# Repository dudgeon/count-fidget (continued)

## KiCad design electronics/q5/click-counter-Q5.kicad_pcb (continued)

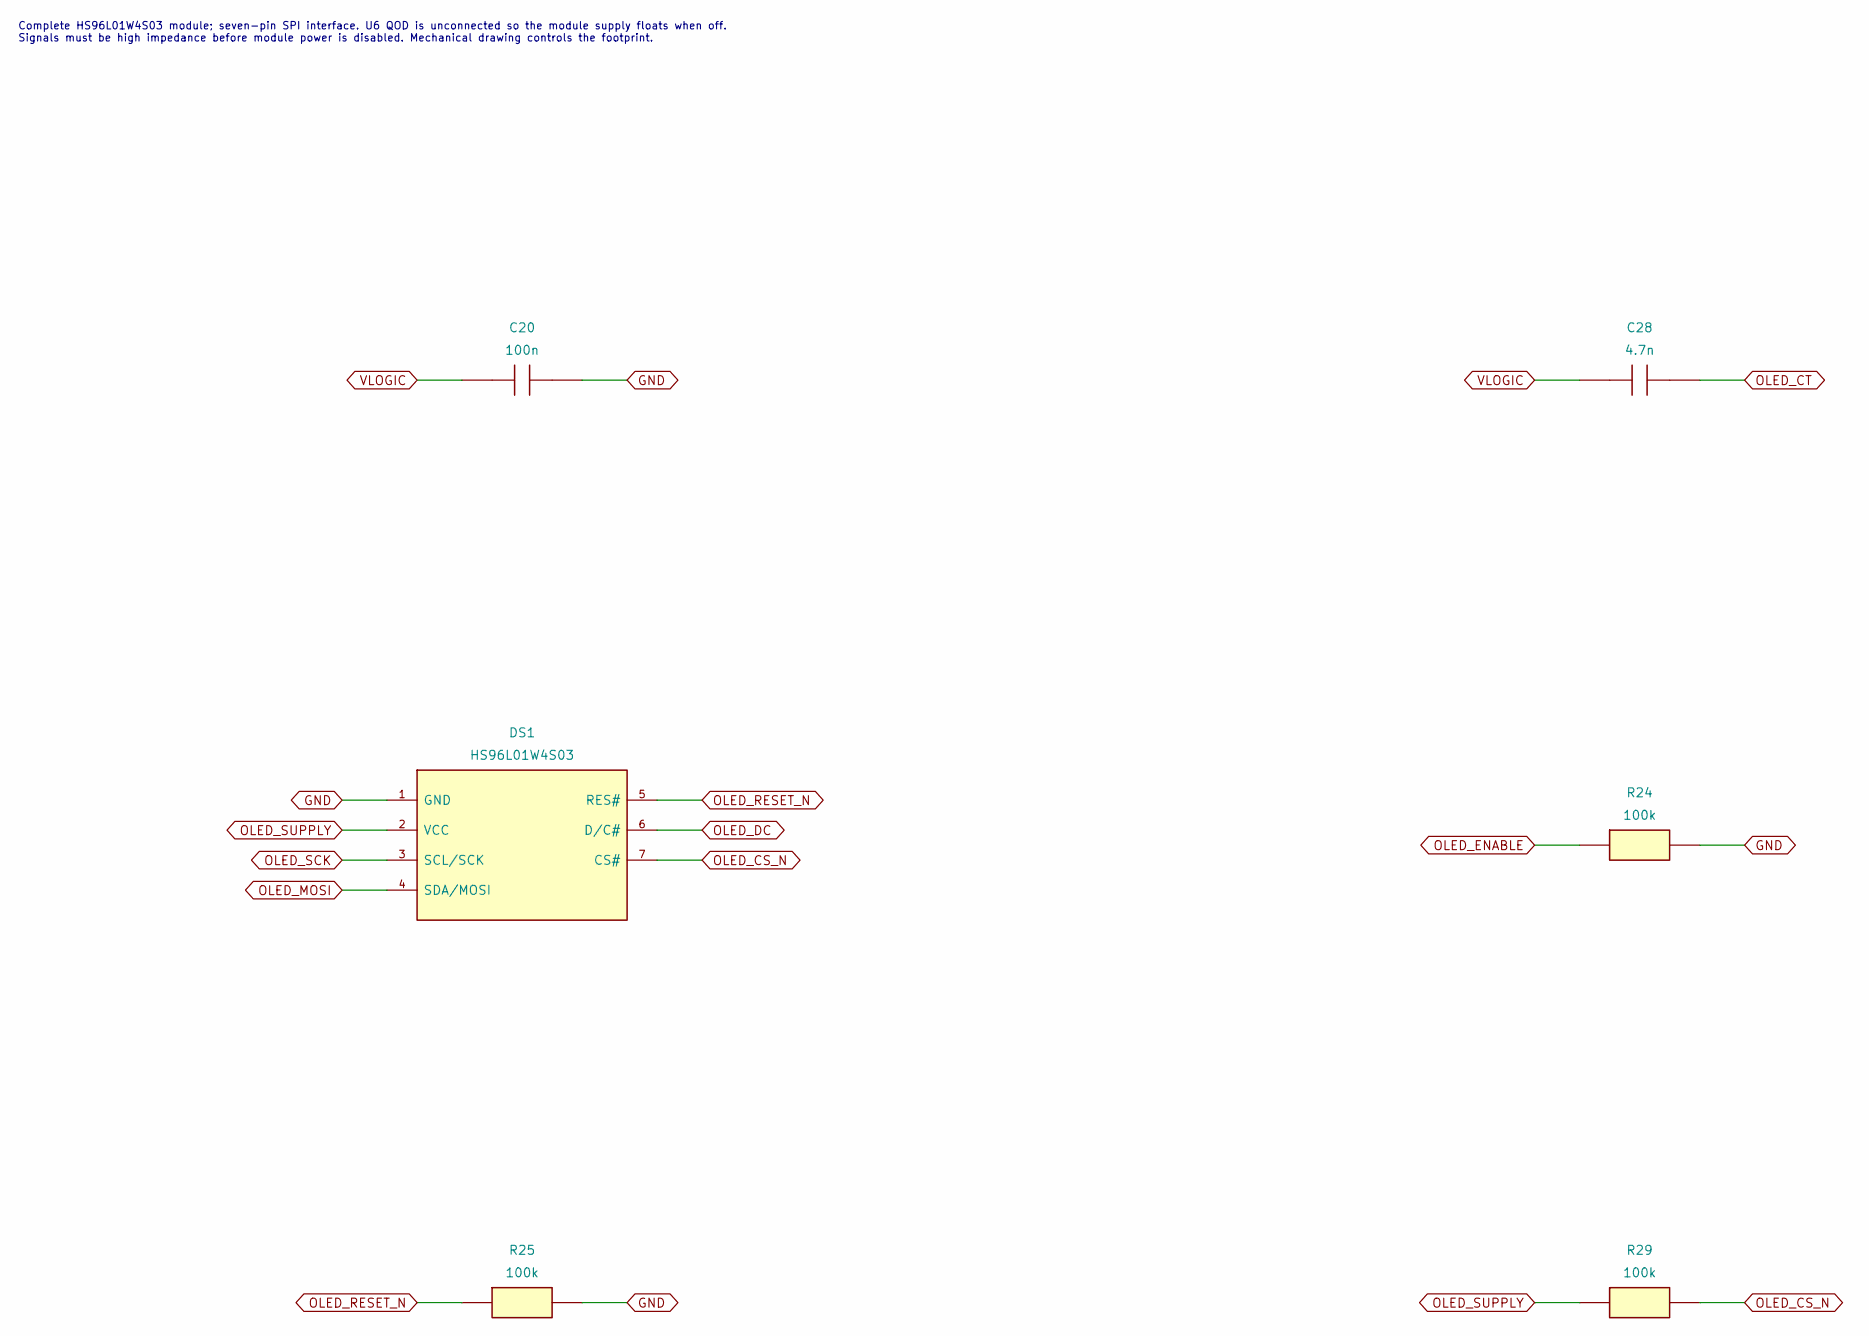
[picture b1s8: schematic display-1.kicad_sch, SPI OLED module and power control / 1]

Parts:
C20: 100n; Capacitor_SMD_C_0603_1608Metric; MPN CC0603KRX7R9BB104
C28: 4.7n; Capacitor_SMD_C_0603_1608Metric; MPN 0603B472K500NT
DS1: SPI OLED module 128x64; HS96L01W4S03_Module_7Pin; MPN HS96L01W4S03
R24, R25, R29: 100k; Resistor_SMD_R_0603_1608Metric; MPN 0603WAF1003T5E

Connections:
GND: C20.2, DS1.1 (GND), R24.2, R25.2; also elsewhere on the board
OLED_CS_N: DS1.7 (CS#), R29.2; also elsewhere on the board
OLED_CT: C28.2; also elsewhere on the board
OLED_DC: DS1.6 (D/C#); also elsewhere on the board
OLED_ENABLE: R24.1; also elsewhere on the board
OLED_MOSI: DS1.4 (SDA/MOSI); also elsewhere on the board
OLED_RESET_N: DS1.5 (RES#), R25.1; also elsewhere on the board
OLED_SCK: DS1.3 (SCL/SCK); also elsewhere on the board
OLED_SUPPLY: DS1.2 (VCC), R29.1; also elsewhere on the board
VLOGIC: C20.1, C28.1; also elsewhere on the board

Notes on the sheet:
Complete HS96L01W4S03 module; seven-pin SPI interface. U6 QOD is unconnected so the module supply floats when off. Signals must be high impedance before module power is disabled. Mechanical drawing controls the footprint.

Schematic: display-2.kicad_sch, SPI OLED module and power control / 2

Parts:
U6: OLED power slew switch; Package_TO_SOT_SMD_SOT-23-6; MPN TPS22917DBVR

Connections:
GND: U6.2 (GND); also elsewhere on the board
OLED_CT: U6.4 (CT); also elsewhere on the board
OLED_ENABLE: U6.3 (ON); also elsewhere on the board
OLED_SUPPLY: U6.6 (VOUT); also elsewhere on the board
VLOGIC: U6.1 (VIN); also elsewhere on the board

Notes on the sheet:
Complete HS96L01W4S03 module; seven-pin SPI interface. U6 QOD is unconnected so the module supply floats when off. Signals must be high impedance before module power is disabled. Mechanical drawing controls the footprint.

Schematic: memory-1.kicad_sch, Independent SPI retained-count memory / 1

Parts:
C30: 10u; Capacitor_SMD_C_0805_2012Metric; MPN GRM21BR61H106KE43L
C36: 100n; Capacitor_SMD_C_0603_1608Metric; MPN CC0603KRX7R9BB104
R32: 75; Resistor_SMD_R_0603_1608Metric; MPN 0603WAF750JT5E
R33: 100k; Resistor_SMD_R_0603_1608Metric; MPN 0603WAF1003T5E
U8: SPI F-RAM 32KiB; Package_SO_SOIC-8_3.9x4.9mm_P1.27mm; MPN FM25V02A-GTR

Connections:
FRAM_CS_N: R33.2, U8.1 (CS#); also elsewhere on the board
FRAM_MISO: U8.2 (SO); also elsewhere on the board
FRAM_MOSI: U8.5 (SI); also elsewhere on the board
FRAM_SCK: U8.6 (SCK); also elsewhere on the board
GND: C30.2, C36.2, U8.4 (VSS); also elsewhere on the board
VFRAM: C30.1, C36.1, R32.2, R33.1, U8.3 (WP#), U8.7 (HOLD#), U8.8 (VDD)
VLOGIC: R32.1; also elsewhere on the board

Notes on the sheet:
FM25V02A F-RAM on an isolated RC supply; dedicated SPI1. Power-ramp, chip-select and interrupted-write behavior require separate analysis and physical qualification.

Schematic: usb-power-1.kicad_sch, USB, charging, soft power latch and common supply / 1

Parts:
C1, C3: 2.2u; Capacitor_SMD_C_0805_2012Metric; MPN CL21A225KBQNNNE
C2: 10u; Capacitor_SMD_C_0805_2012Metric; MPN GRM21BR61H106KE43L
C13, C29: 4.7n; Capacitor_SMD_C_0603_1608Metric; MPN 0603B472K500NT
C38: 100n; Capacitor_SMD_C_0603_1608Metric; MPN CC0603KRX7R9BB104

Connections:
CELL_P: C3.1; also elsewhere on the board
GND: C1.2, C2.2, C3.2, C13.2, C38.2; also elsewhere on the board
RC_COMP: C13.1; also elsewhere on the board
SYS: C2.1, C29.1; also elsewhere on the board
SYS_CT: C29.2; also elsewhere on the board
VBUS: C1.1, C38.1; also elsewhere on the board

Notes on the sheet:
U7 ON = VBUS (D4) OR COUNT key (D3 A1) OR PWR_HOLD (D3 A2), pulled down by R35. Off: only BQ29700 and BQ25185 battery quiescent current remain. Cold cell insertion is not proven by the slew switch.

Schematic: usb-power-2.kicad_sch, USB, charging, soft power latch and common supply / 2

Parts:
C5: 2.2u; Capacitor_SMD_C_0805_2012Metric; MPN CL21A225KBQNNNE
C39: 100n; Capacitor_SMD_C_0603_1608Metric; MPN CC0603KRX7R9BB104
C40: 10n; Capacitor_SMD_C_0603_1608Metric; MPN 0603B103K500NT
D1, D2: USB ESD; Package_TO_SOT_SMD_SOT-23-6; MPN USBLC6-2SC6
D3: BAT54C; Package_TO_SOT_SMD_SOT-23; MPN BAT54C,215

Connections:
CC1: D1.1 (I/O1), D1.6 (I/O1); also elsewhere on the board
CC2: D1.3 (I/O2), D1.4 (I/O2); also elsewhere on the board
GND: C5.2, C39.2, C40.2, D1.2 (GND), D2.2 (GND); also elsewhere on the board
PWR_HOLD: D3.2 (A2); also elsewhere on the board
PWR_KEY: D3.1 (A1); also elsewhere on the board
SYS_LOAD: C5.1; also elsewhere on the board
SYS_ON: C40.1, D3.3 (K); also elsewhere on the board
USB_DM: D2.1 (I/O1), D2.6 (I/O1); also elsewhere on the board
USB_DP: D2.3 (I/O2), D2.4 (I/O2); also elsewhere on the board
VBUS: C39.1, D1.5 (VBUS), D2.5 (VBUS); also elsewhere on the board

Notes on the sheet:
U7 ON = VBUS (D4) OR COUNT key (D3 A1) OR PWR_HOLD (D3 A2), pulled down by R35. Off: only BQ29700 and BQ25185 battery quiescent current remain. Cold cell insertion is not proven by the slew switch.

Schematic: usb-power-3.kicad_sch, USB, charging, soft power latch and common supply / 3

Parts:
D4: 1N4148WS; Diode_SMD_D_SOD-323; MPN 1N4148WS
J1: USB-C power and DFU; Connector_USB_USB_C_Receptacle_GCT_USB4105-xx-A_16P_TopMnt_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; MPN USB4105-GF-A-120
R1, R2: 5.1k; Resistor_SMD_R_0603_1608Metric; MPN 0603WAF5101T5E
R3: 24k; Resistor_SMD_R_0603_1608Metric; MPN 0603WAF2402T5E
R19: 2k; Resistor_SMD_R_0603_1608Metric; MPN 0603WAF2001T5E

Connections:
CC1: J1.A5 (CCA), R1.1; also elsewhere on the board
CC2: J1.B5 (CCB), R2.1; also elsewhere on the board
GND: J1.A1 (GND), J1.A12 (GND), J1.B1 (GND), J1.B12 (GND), J1.SH (SHIELD), R1.2, R2.2, R3.2; also elsewhere on the board
ISET: R19.1; also elsewhere on the board
RC_COMP: R19.2; also elsewhere on the board
USB_DM: J1.A7 (D-), J1.B7 (D-); also elsewhere on the board
USB_DP: J1.A6 (D+), J1.B6 (D+); also elsewhere on the board
VBUS: D4.2 (A), J1.A4 (VBUS), J1.A9 (VBUS), J1.B4 (VBUS), J1.B9 (VBUS); also elsewhere on the board
VBUS_WAKE: D4.1 (K); also elsewhere on the board
VSET: R3.1; also elsewhere on the board

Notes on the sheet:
U7 ON = VBUS (D4) OR COUNT key (D3 A1) OR PWR_HOLD (D3 A2), pulled down by R35. Off: only BQ29700 and BQ25185 battery quiescent current remain. Cold cell insertion is not proven by the slew switch.

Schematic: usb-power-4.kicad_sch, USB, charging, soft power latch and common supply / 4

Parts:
R4: 18k; Resistor_SMD_R_0603_1608Metric; MPN 0603WAF1802T5E
R30: 150k; Resistor_SMD_R_0603_1608Metric; MPN RT0603BRD07150KL
R31: 49.9k; Resistor_SMD_R_0603_1608Metric; MPN RT0603BRD0749K9L
R34, R38: 100k; Resistor_SMD_R_0603_1608Metric; MPN 0603WAF1003T5E
R35: 1M; Resistor_SMD_R_0603_1608Metric; MPN 0603WAF1004T5E

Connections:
GND: R4.2, R31.2, R34.2, R35.2; also elsewhere on the board
ISET: R4.1; also elsewhere on the board
PWR_KEY: R34.1; also elsewhere on the board
SYS_ON: R35.1, R38.2; also elsewhere on the board
VBUS_WAKE: R38.1; also elsewhere on the board
VLOGIC: R30.1; also elsewhere on the board
VLOGIC_FB: R30.2, R31.1; also elsewhere on the board

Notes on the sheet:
U7 ON = VBUS (D4) OR COUNT key (D3 A1) OR PWR_HOLD (D3 A2), pulled down by R35. Off: only BQ29700 and BQ25185 battery quiescent current remain. Cold cell insertion is not proven by the slew switch.

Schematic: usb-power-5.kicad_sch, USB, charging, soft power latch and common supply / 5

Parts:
R5: 10k; Resistor_SMD_R_0603_1608Metric; MPN 0603WAF1002T5E
R6: 100k; Resistor_SMD_R_0603_1608Metric; MPN 0603WAF1003T5E
TP13: SYS_ON; TestPoint_TestPoint_Pad_D1.5mm; MPN PCB LAND
U2: Li-ion charger; Package_DFN_QFN_Texas_DLH0010A_WSON-10-1EP_2.2x2mm_P0.4mm_E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; MPN BQ25185DLHR
U3: 3.20481V adjustable LDO; Package_SON_WSON-6-1EP_2x2mm_P0.65mm_EP1x1.6mm; MPN TLV76701DRVR
U7: System soft-power latch switch; Package_TO_SOT_SMD_SOT-23-6; MPN TPS22917DBVR

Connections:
CELL_P: U2.2 (BAT); also elsewhere on the board
CE_N: R6.2, U2.4 (~CE); also elsewhere on the board
CHG_STAT1: U2.9 (STAT1); also elsewhere on the board
CHG_STAT2: U2.3 (STAT2); also elsewhere on the board
GND: R5.2, U2.5 (GND), U2.11 (EP/GND), U3.3 (GND), U3.5 (GND), U3.7 (EP), U7.2 (GND); also elsewhere on the board
ISET: U2.8 (ISET); also elsewhere on the board
SYS: U2.1 (SYS), U7.1 (VIN); also elsewhere on the board
SYS_CT: U7.4 (CT); also elsewhere on the board
SYS_LOAD: U3.4 (EN), U3.6 (IN), U7.6 (VOUT); also elsewhere on the board
SYS_ON: TP13.1 (1_1), U7.3 (ON); also elsewhere on the board
TS_FIXED: R5.1, U2.6 (TS/MR)
VBUS: R6.1, U2.10 (IN); also elsewhere on the board
VLOGIC: U3.1 (OUT); also elsewhere on the board
VLOGIC_FB: U3.2 (FB); also elsewhere on the board
VSET: U2.7 (ILIM/VSET); also elsewhere on the board

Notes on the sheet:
U7 ON = VBUS (D4) OR COUNT key (D3 A1) OR PWR_HOLD (D3 A2), pulled down by R35. Off: only BQ29700 and BQ25185 battery quiescent current remain. Cold cell insertion is not proven by the slew switch.

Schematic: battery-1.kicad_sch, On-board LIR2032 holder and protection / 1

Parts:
BT1: LIR2032 holder; BatteryHolder_QJ_CR2032-BS-6-1; MPN CR2032-BS-6-1
C4: 100n; Capacitor_SMD_C_0603_1608Metric; MPN CC0603KRX7R9BB104
Q1: Discharge FET; Package_TO_SOT_SMD_SOT-23; MPN AO3400A
Q2: Charge FET; Package_TO_SOT_SMD_SOT-23; MPN AO3400A
R7: 330; Resistor_SMD_R_0603_1608Metric; MPN 0603WAF3300T5E
R8: 2.2k; Resistor_SMD_R_0603_1608Metric; MPN 0603WAF2201T5E

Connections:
BAT_SENSE: C4.1, R7.2; also elsewhere on the board
CELL_N_RAW: BT1.2 (-), C4.2, Q1.2 (S); also elsewhere on the board
CELL_P: BT1.1 (+), R7.1; also elsewhere on the board
COUT: Q2.1 (G); also elsewhere on the board
DOUT: Q1.1 (G); also elsewhere on the board
FET_DRAIN: Q1.3 (D), Q2.3 (D)
GND: R8.1; also elsewhere on the board
SENSE_FET: Q2.2 (S); also elsewhere on the board
VMINUS: R8.2; also elsewhere on the board

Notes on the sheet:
CELL_N_RAW is isolated from system ground by the protection path. BT1 accepts the rechargeable LIR2032 only. Cell compatibility, protection, USB rearm and cold insertion remain qualification gates.

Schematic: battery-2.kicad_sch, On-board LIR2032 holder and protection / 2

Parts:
R9: 3.3; Resistor_SMD_R_0603_1608Metric; MPN 0603WAF330KT5E
U4: Cell protector; Package_SON_WSON-6_1.5x1.5mm_P0.5mm; MPN BQ29700DSER

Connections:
BAT_SENSE: U4.5 (BAT); also elsewhere on the board
CELL_N_RAW: U4.4 (VSS); also elsewhere on the board
COUT: U4.2 (COUT); also elsewhere on the board
DOUT: U4.3 (DOUT); also elsewhere on the board
GND: R9.2; also elsewhere on the board
SENSE_FET: R9.1; also elsewhere on the board
VMINUS: U4.6 (V-); also elsewhere on the board

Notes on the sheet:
CELL_N_RAW is isolated from system ground by the protection path. BT1 accepts the rechargeable LIR2032 only. Cell compatibility, protection, USB rearm and cold insertion remain qualification gates.

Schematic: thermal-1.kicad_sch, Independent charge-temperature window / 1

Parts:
C9: 100n; Capacitor_SMD_C_0603_1608Metric; MPN CC0603KRX7R9BB104
Q3: Charge enable; Package_TO_SOT_SMD_SOT-23; MPN 2N7002
Q4: Charge enable hot gate; Package_TO_SOT_SMD_SOT-23; MPN 2N7002
R10: 56k; Resistor_SMD_R_0603_1608Metric; MPN 0603WAF5602T5E
R11: 82k; Resistor_SMD_R_0603_1608Metric; MPN 0603WAF8202T5E
R12: 18k; Resistor_SMD_R_0603_1608Metric; MPN 0603WAF1802T5E

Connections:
CE_MID: Q3.2 (S), Q4.3 (D)
CE_N: Q3.3 (D); also elsewhere on the board
GND: C9.2, Q4.2 (S); also elsewhere on the board
TEMP_COLD: R11.2, R12.1; also elsewhere on the board
TEMP_COLD_OK: Q3.1 (G); also elsewhere on the board
TEMP_HOT: R12.2; also elsewhere on the board
TEMP_HOT_OK: Q4.1 (G); also elsewhere on the board
TEMP_SENSE: R10.2; also elsewhere on the board
U5_VCC: C9.1; also elsewhere on the board
VBUS: R10.1, R11.1; also elsewhere on the board

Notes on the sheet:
TH1 on the board beside BT1; both window outputs must enable their series FETs for charging. Gate pulldowns disable charging when comparator power is absent; threshold and fault tests remain required.

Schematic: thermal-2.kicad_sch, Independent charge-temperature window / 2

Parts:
R13: 12k; Resistor_SMD_R_0603_1608Metric; MPN 0603WAF1202T5E
R14, R15: 100k; Resistor_SMD_R_0603_1608Metric; MPN 0603WAF1003T5E
R39: 1k; Resistor_SMD_R_0603_1608Metric; MPN 0603WAF1001T5E
TH1: 10k NTC B3380; Resistor_SMD_R_0603_1608Metric; MPN NCP18XH103F03RB
U5: Push-pull temperature window; Package_TO_SOT_SMD_SOT-23-8; MPN TLV7012DDFR

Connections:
GND: R13.2, R14.2, R15.2, TH1.2, U5.4 (VEE); also elsewhere on the board
TEMP_COLD: U5.3 (INA+); also elsewhere on the board
TEMP_COLD_OK: R14.1, U5.1 (OUTA); also elsewhere on the board
TEMP_HOT: R13.1, U5.6 (INB-); also elsewhere on the board
TEMP_HOT_OK: R15.1, U5.7 (OUTB); also elsewhere on the board
TEMP_SENSE: TH1.1, U5.2 (INA-), U5.5 (INB+); also elsewhere on the board
U5_VCC: R39.2, U5.8 (VCC); also elsewhere on the board
VBUS: R39.1; also elsewhere on the board

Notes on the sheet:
TH1 on the board beside BT1; both window outputs must enable their series FETs for charging. Gate pulldowns disable charging when comparator power is absent; threshold and fault tests remain required.

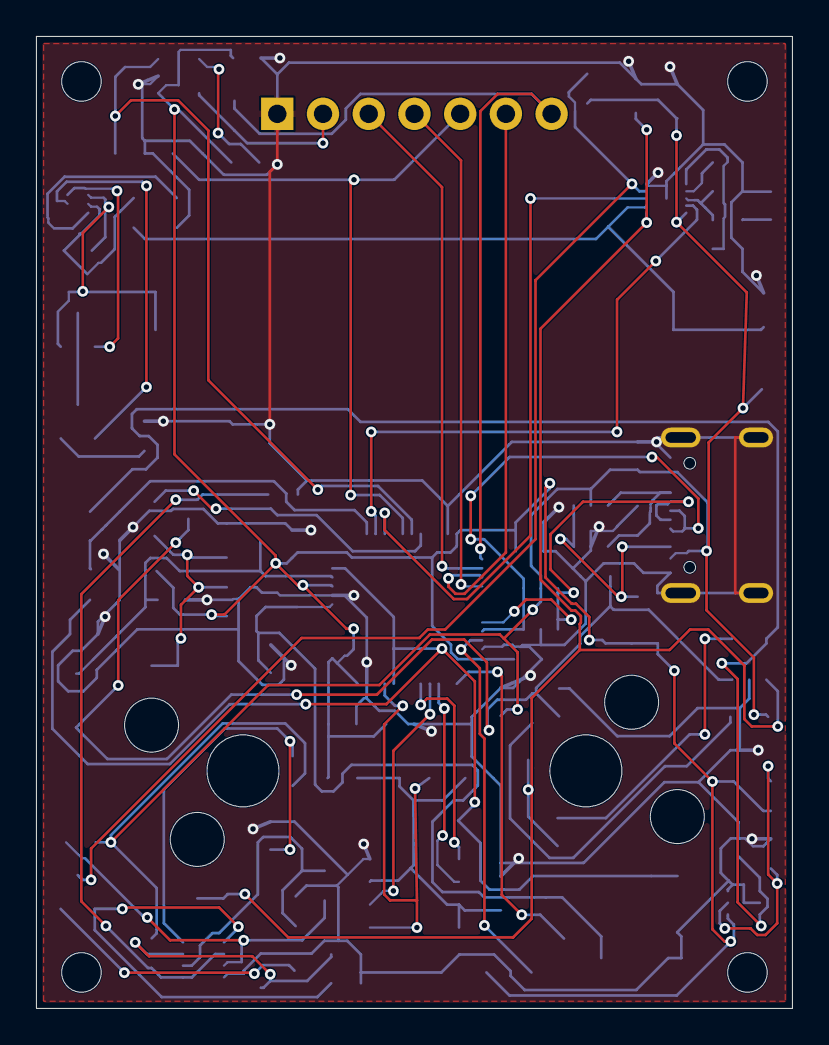
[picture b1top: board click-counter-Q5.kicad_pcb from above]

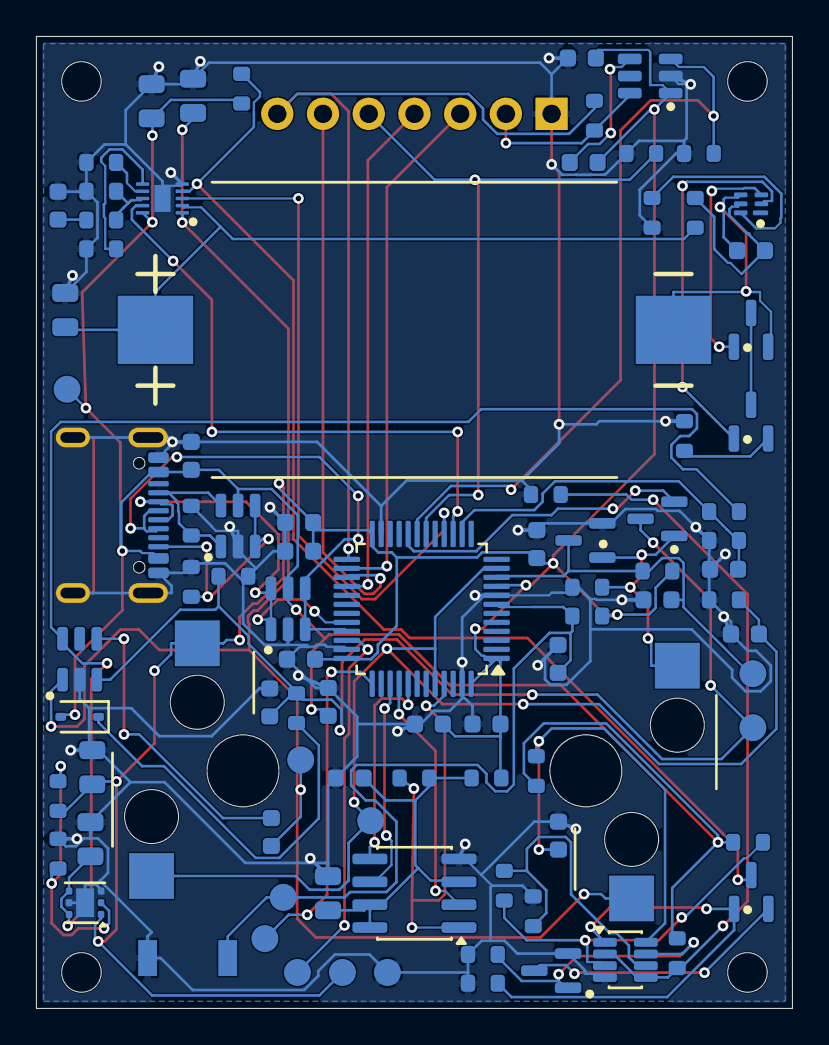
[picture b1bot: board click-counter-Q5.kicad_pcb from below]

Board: 2 copper layers, 42.0 x 54.0 mm, 96 parts (91 on the bottom side), 56 nets.

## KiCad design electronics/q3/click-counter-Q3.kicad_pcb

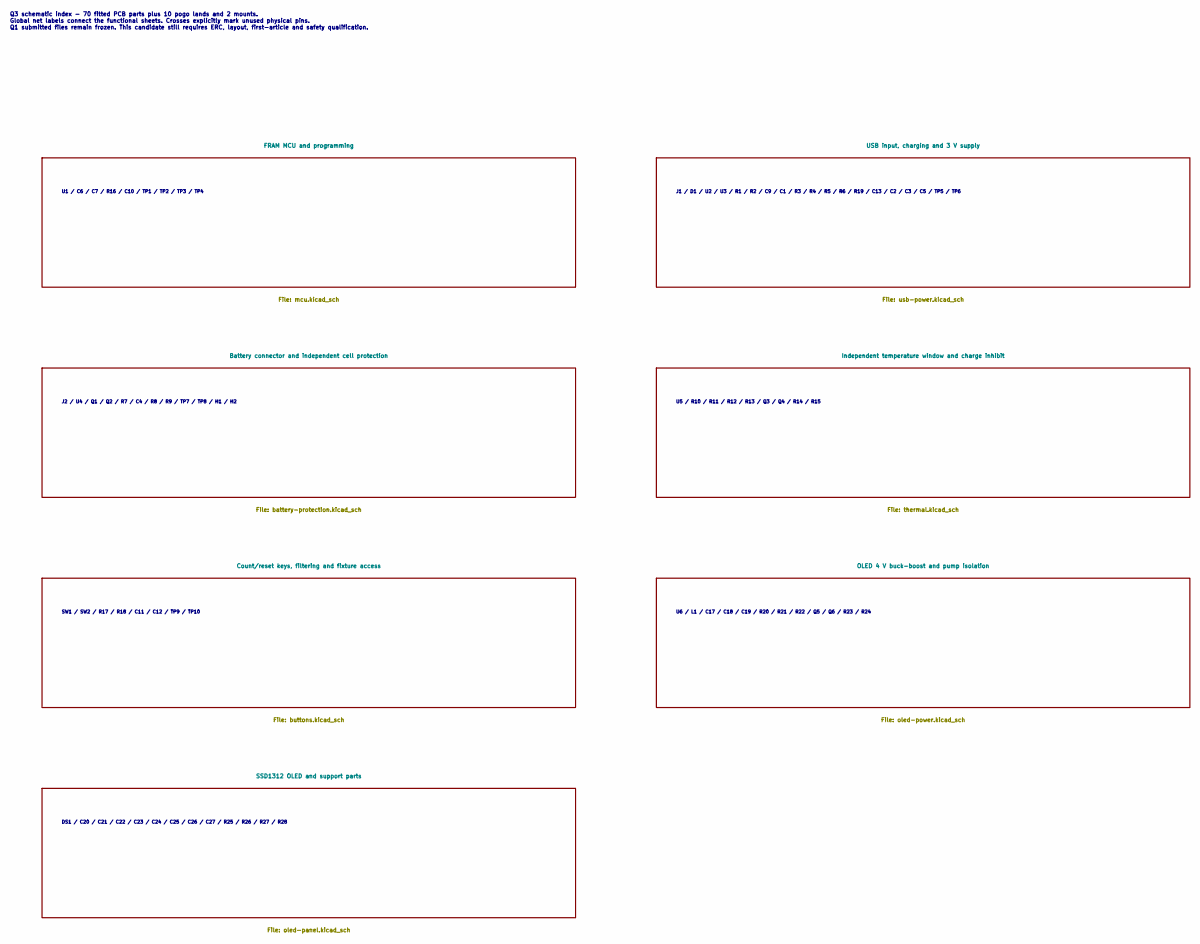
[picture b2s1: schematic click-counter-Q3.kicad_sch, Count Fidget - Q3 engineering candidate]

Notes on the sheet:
Q3 schematic index - 70 fitted PCB parts plus 10 pogo lands and 2 mounts. Global net labels connect the functional sheets. Crosses explicitly mark unused physical pins. Q1 submitted files remain frozen. This candidate still requires ERC, layout, first-article and safety qualification.
U1 / C6 / C7 / R16 / C10 / TP1 / TP2 / TP3 / TP4
J1 / D1 / U2 / U3 / R1 / R2 / C9 / C1 / R3 / R4 / R5 / R6 / R19 / C13 / C2 / C3 / C5 / TP5 / TP6
J2 / U4 / Q1 / Q2 / R7 / C4 / R8 / R9 / TP7 / TP8 / H1 / H2
U5 / R10 / R11 / R12 / R13 / Q3 / Q4 / R14 / R15
SW1 / SW2 / R17 / R18 / C11 / C12 / TP9 / TP10
U6 / L1 / C17 / C18 / C19 / R20 / R21 / R22 / Q5 / Q6 / R23 / R24
DS1 / C20 / C21 / C22 / C23 / C24 / C25 / C26 / C27 / R25 / R26 / R27 / R28

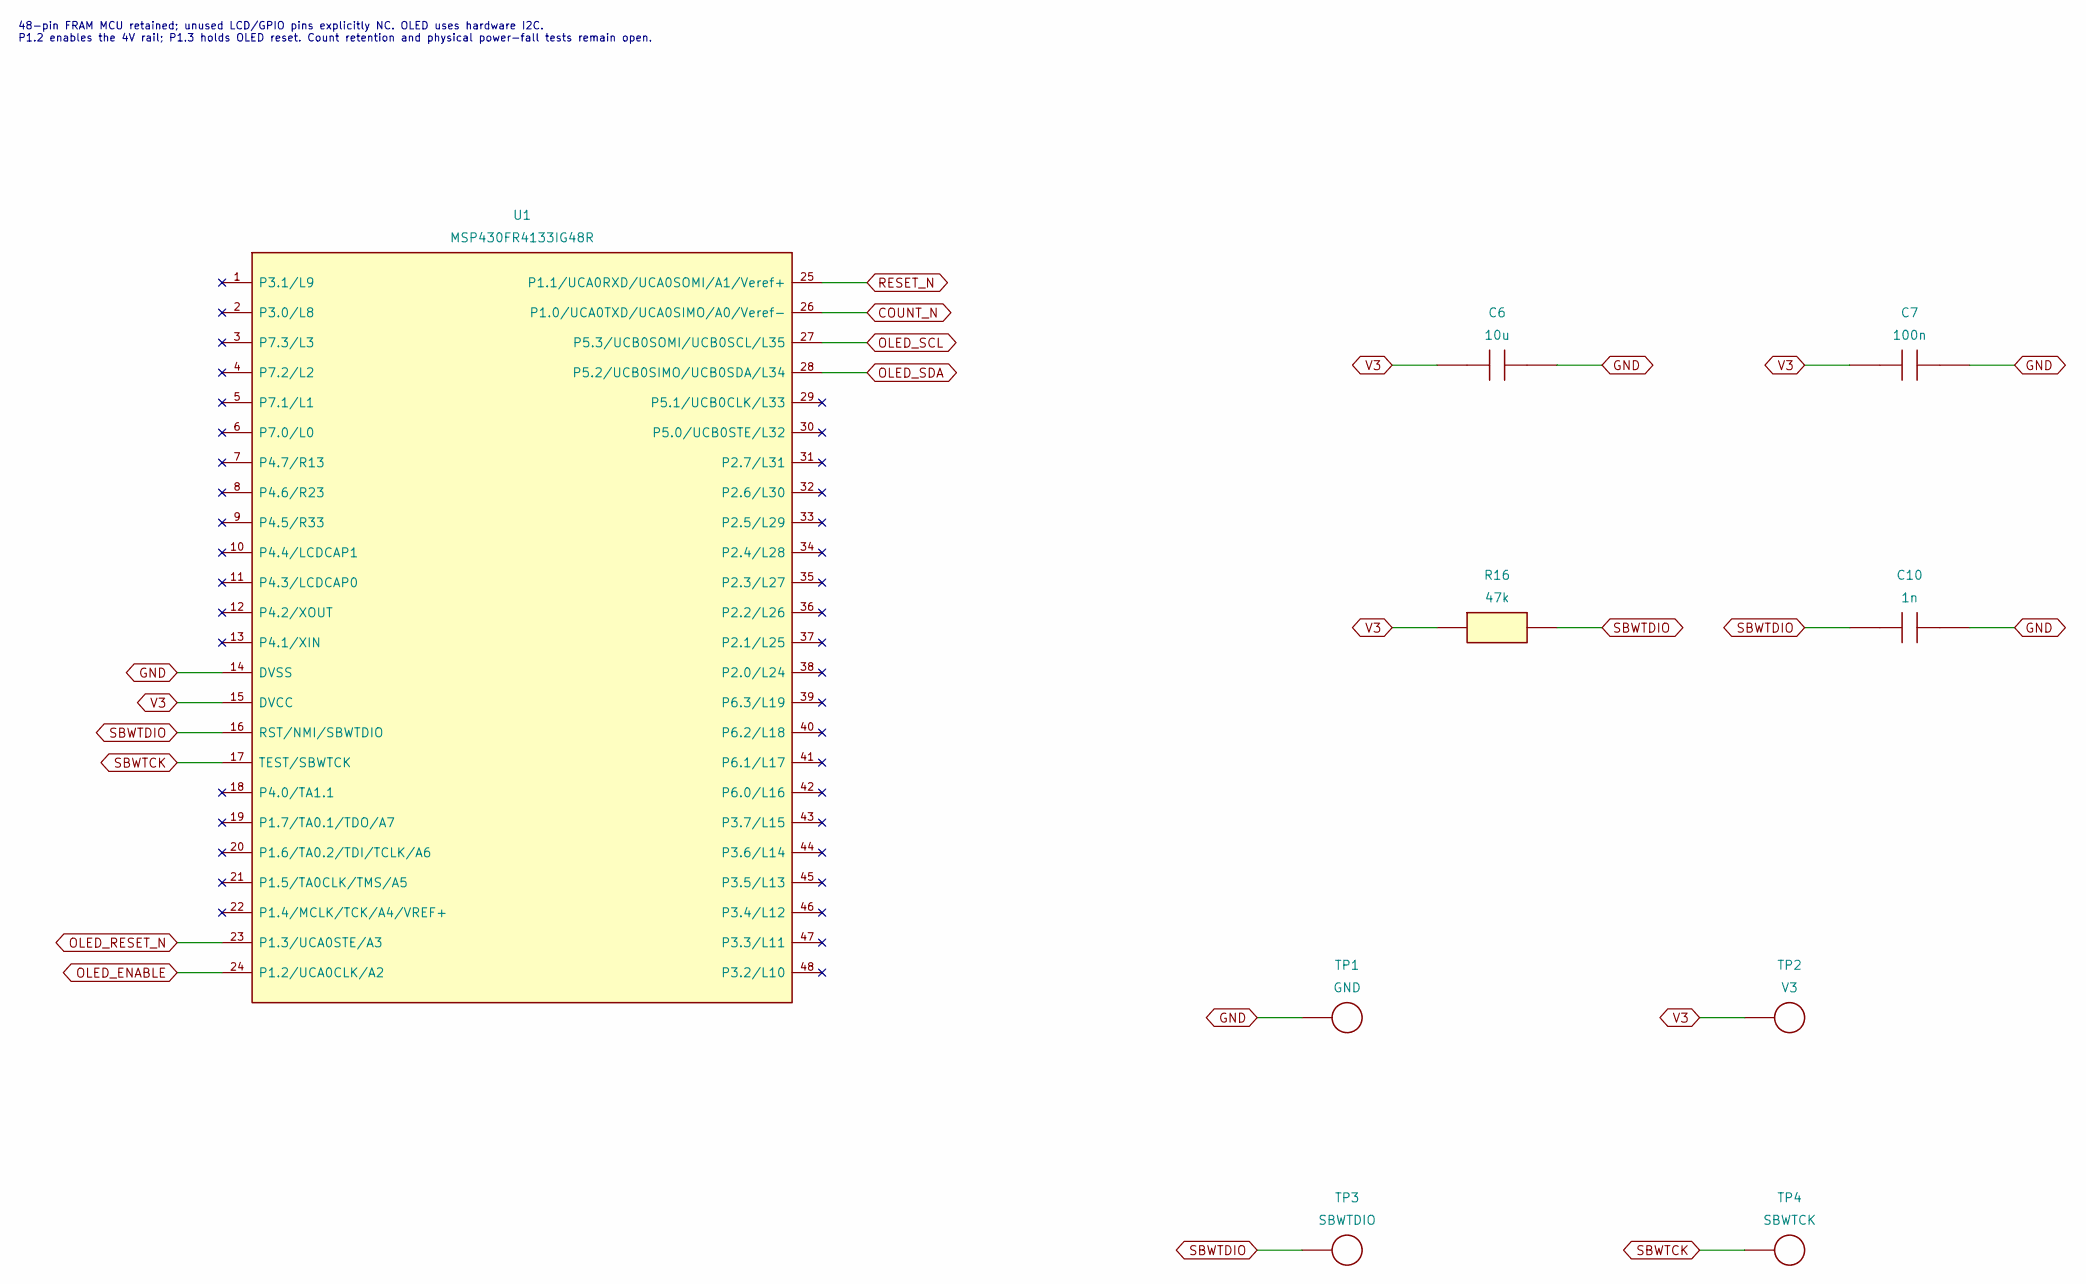
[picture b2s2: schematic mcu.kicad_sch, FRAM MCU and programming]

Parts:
C6: 10u; Capacitor_SMD_C_0805_2012Metric; MPN GRM21BR61E106KA73L
C7: 100n; Capacitor_SMD_C_0603_1608Metric; MPN GRM188R71H104KA93D
C10: 1n; Capacitor_SMD_C_0603_1608Metric; MPN GRM1885C1H102JA01D
R16: 47k; Resistor_SMD_R_0603_1608Metric; MPN 0603WAF4702T5E
TP1: GND; TestPoint_TestPoint_Pad_D1.5mm; MPN PCB LAND
TP2: V3; TestPoint_TestPoint_Pad_D1.5mm; MPN PCB LAND
TP3: SBWTDIO; TestPoint_TestPoint_Pad_D1.5mm; MPN PCB LAND
TP4: SBWTCK; TestPoint_TestPoint_Pad_D1.5mm; MPN PCB LAND
U1: MSP430FR4133; Package_SO_TSSOP-48_6.1x12.5mm_P0.5mm; MPN MSP430FR4133IG48R

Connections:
COUNT_N: U1.26 (P1.0/UCA0TXD/UCA0SIMO/A0/Veref-); also elsewhere on the board
GND: C6.2, C7.2, C10.2, TP1.1 (1_1), U1.14 (DVSS); also elsewhere on the board
OLED_ENABLE: U1.24 (P1.2/UCA0CLK/A2); also elsewhere on the board
OLED_RESET_N: U1.23 (P1.3/UCA0STE/A3); also elsewhere on the board
OLED_SCL: U1.27 (P5.3/UCB0SOMI/UCB0SCL/L35); also elsewhere on the board
OLED_SDA: U1.28 (P5.2/UCB0SIMO/UCB0SDA/L34); also elsewhere on the board
RESET_N: U1.25 (P1.1/UCA0RXD/UCA0SOMI/A1/Veref+); also elsewhere on the board
SBWTCK: TP4.1 (1_1), U1.17 (TEST/SBWTCK)
SBWTDIO: C10.1, R16.2, TP3.1 (1_1), U1.16 (RST/NMI/SBWTDIO)
V3: C6.1, C7.1, R16.1, TP2.1 (1_1), U1.15 (DVCC); also elsewhere on the board

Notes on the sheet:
48-pin FRAM MCU retained; unused LCD/GPIO pins explicitly NC. OLED uses hardware I2C. P1.2 enables the 4V rail; P1.3 holds OLED reset. Count retention and physical power-fall tests remain open.

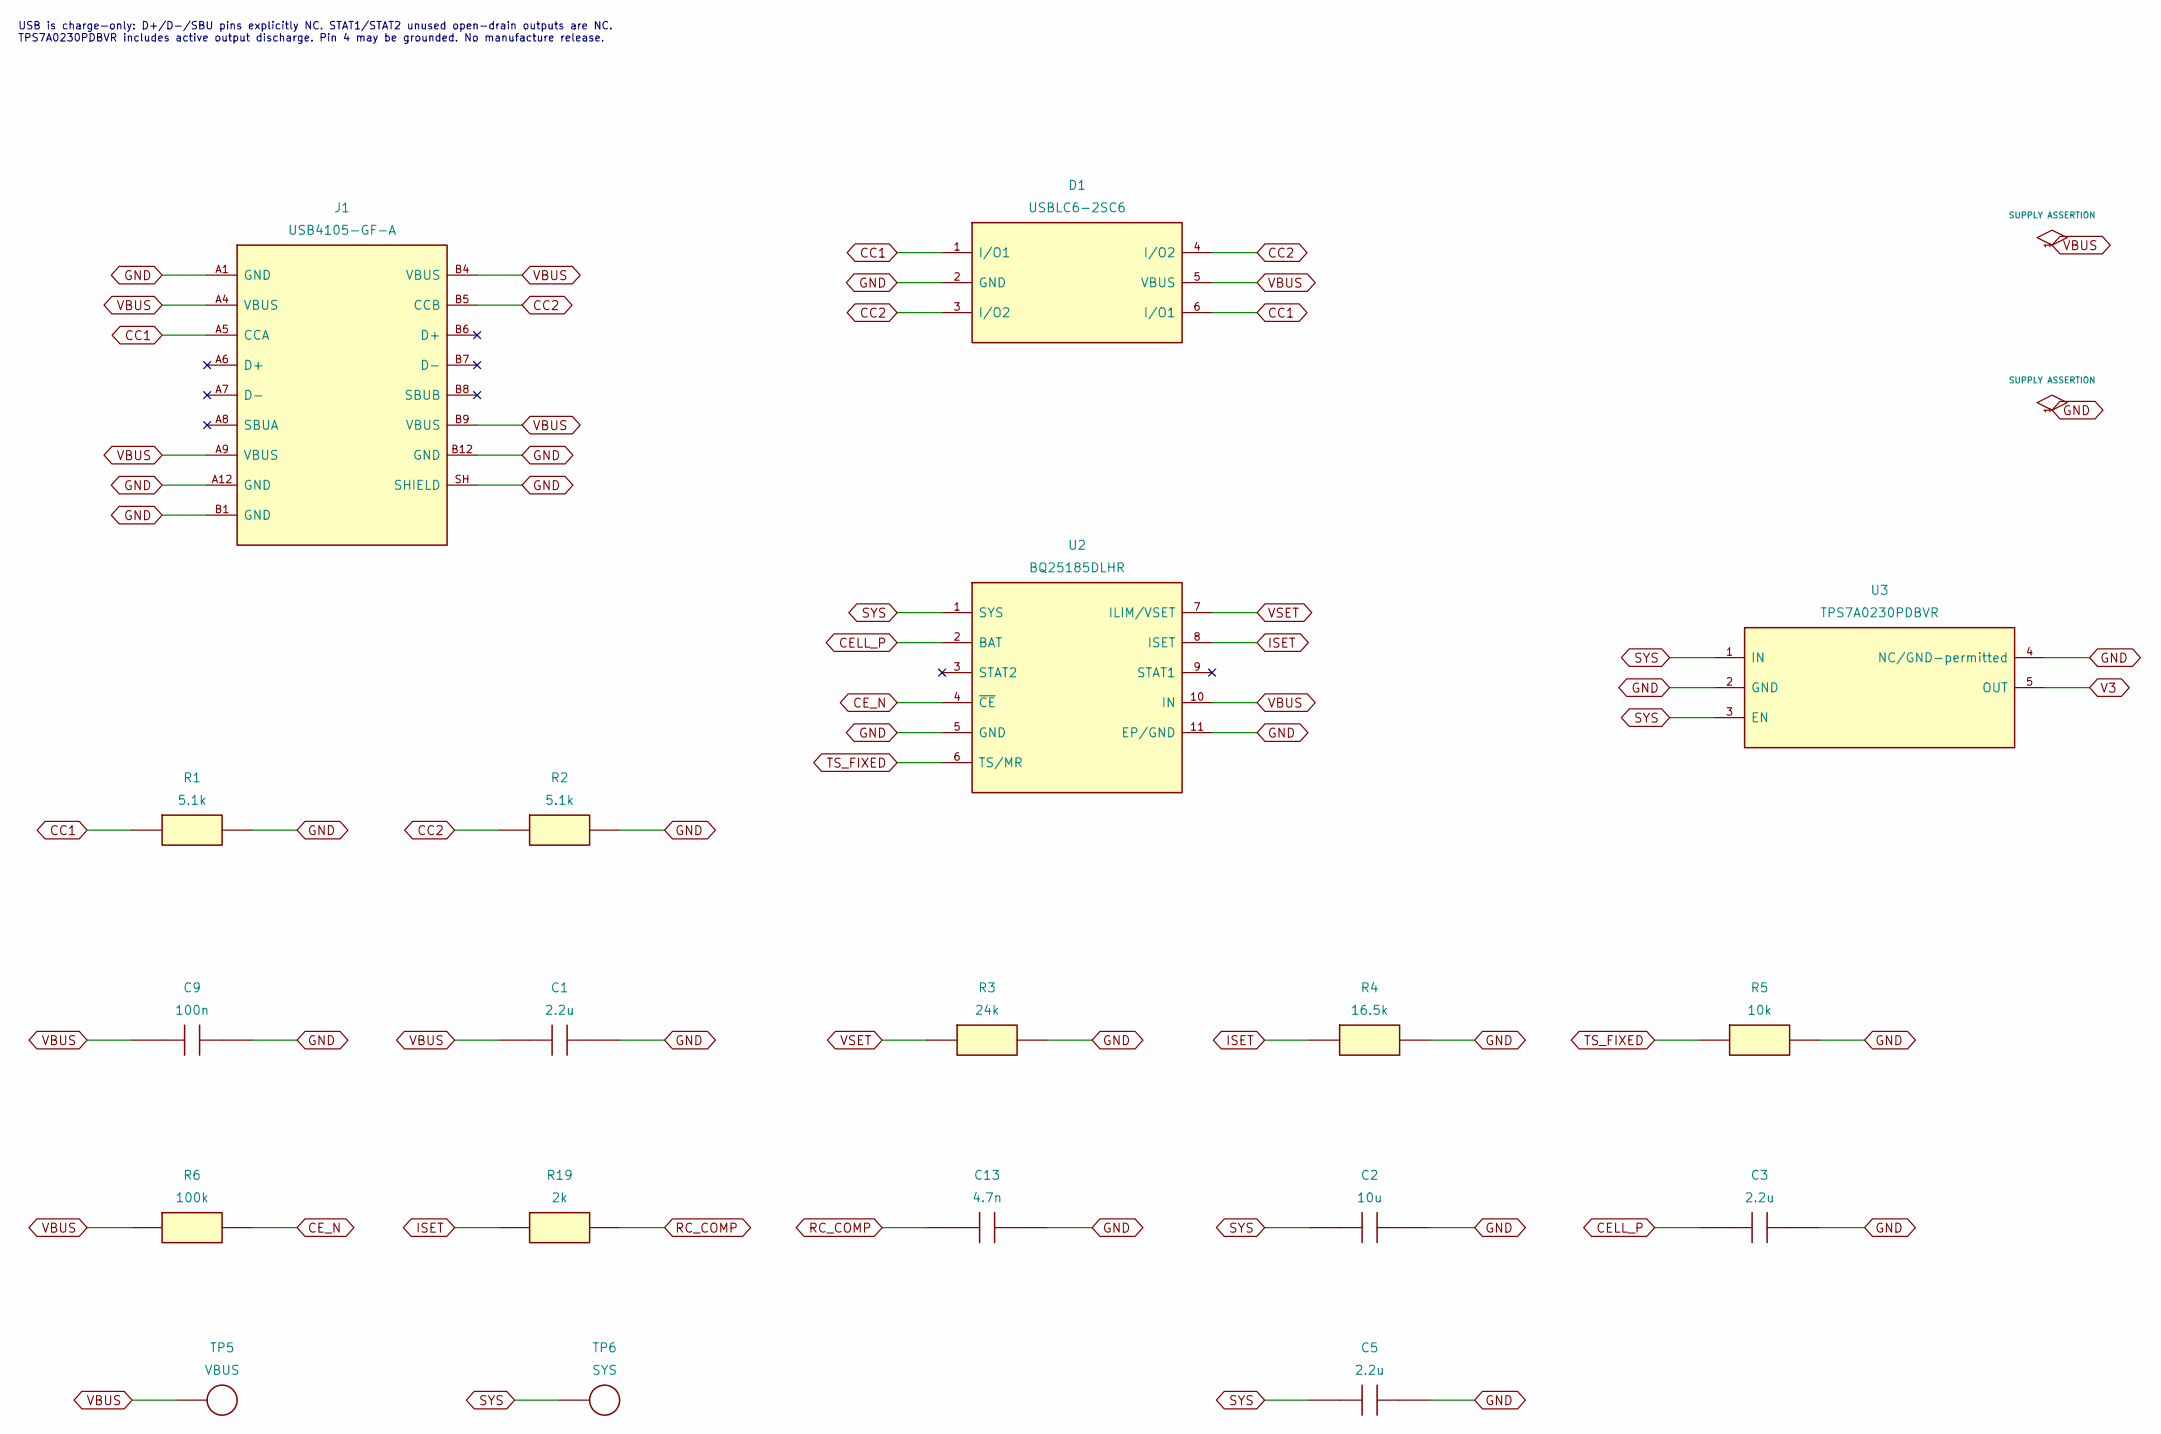
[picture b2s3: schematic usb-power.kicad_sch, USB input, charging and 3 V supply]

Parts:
C1, C3, C5: 2.2u; Capacitor_SMD_C_0805_2012Metric; MPN GRM21BR71E225KE11L
C2: 10u; Capacitor_SMD_C_0805_2012Metric; MPN GRM21BR61E106KA73L
C9: 100n; Capacitor_SMD_C_0603_1608Metric; MPN GRM188R71H104KA93D
C13: 4.7n; Capacitor_SMD_C_0603_1608Metric; MPN GRM1885C1H472JA01D
D1: USB ESD; Package_TO_SOT_SMD_SOT-23-6; MPN USBLC6-2SC6
J1: USB-C charge; Connector_USB_USB_C_Receptacle_GCT_USB4105-xx-A_16P_TopMnt_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; MPN USB4105-GF-A
R1, R2: 5.1k; Resistor_SMD_R_0603_1608Metric; MPN RC0603FR-075K1L
R3: 24k; Resistor_SMD_R_0603_1608Metric; MPN 0603WAF2402T5E
R4: 16.5k; Resistor_SMD_R_0603_1608Metric; MPN RC0603FR-0716K5L
R5: 10k; Resistor_SMD_R_0603_1608Metric; MPN RC0603FR-0710KL
R6: 100k; Resistor_SMD_R_0603_1608Metric; MPN RC0603FR-07100KL
R19: 2k; Resistor_SMD_R_0603_1608Metric; MPN RC0603FR-072KL
TP5: VBUS; TestPoint_TestPoint_Pad_D1.5mm; MPN PCB LAND
TP6: SYS; TestPoint_TestPoint_Pad_D1.5mm; MPN PCB LAND
U2: Li-ion charger; Package_DFN_QFN_Texas_DLH0010A_WSON-10-1EP_2.2x2mm_P0.4mm_E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; MPN BQ25185DLHR
U3: 3.0 V LDO; Package_TO_SOT_SMD_SOT-23-5; MPN TPS7A0230PDBVR

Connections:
CC1: D1.1 (I/O1), D1.6 (I/O1), J1.A5 (CCA), R1.1
CC2: D1.3 (I/O2), D1.4 (I/O2), J1.B5 (CCB), R2.1
CELL_P: C3.1, U2.2 (BAT); also elsewhere on the board
CE_N: R6.2, U2.4 (~CE); also elsewhere on the board
GND: C1.2, C2.2, C3.2, C5.2, C9.2, C13.2, D1.2 (GND), J1.A1 (GND), J1.A12 (GND), J1.B1 (GND), J1.B12 (GND), J1.SH (SHIELD), R1.2, R2.2, R3.2, R4.2, R5.2, U2.5 (GND), U2.11 (EP/GND), U3.2 (GND), U3.4 (NC/GND-permitted); also elsewhere on the board
ISET: R4.1, R19.1, U2.8 (ISET)
RC_COMP: C13.1, R19.2
SYS: C2.1, C5.1, TP6.1 (1_1), U2.1 (SYS), U3.1 (IN), U3.3 (EN); also elsewhere on the board
TS_FIXED: R5.1, U2.6 (TS/MR)
V3: U3.5 (OUT); also elsewhere on the board
VBUS: C1.1, C9.1, D1.5 (VBUS), J1.A4 (VBUS), J1.A9 (VBUS), J1.B4 (VBUS), J1.B9 (VBUS), R6.1, TP5.1 (1_1), U2.10 (IN); also elsewhere on the board
VSET: R3.1, U2.7 (ILIM/VSET)

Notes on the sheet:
USB is charge-only: D+/D-/SBU pins explicitly NC. STAT1/STAT2 unused open-drain outputs are NC. TPS7A0230PDBVR includes active output discharge. Pin 4 may be grounded. No manufacture release.
